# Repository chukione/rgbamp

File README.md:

# rgbamp
home etched single side rgb video amp for the n64

because my local electronic parts dealer does not sell THS7314 amp, i make this RGB amp to play on a sony PVM, with smd BC817 PNP transistors.

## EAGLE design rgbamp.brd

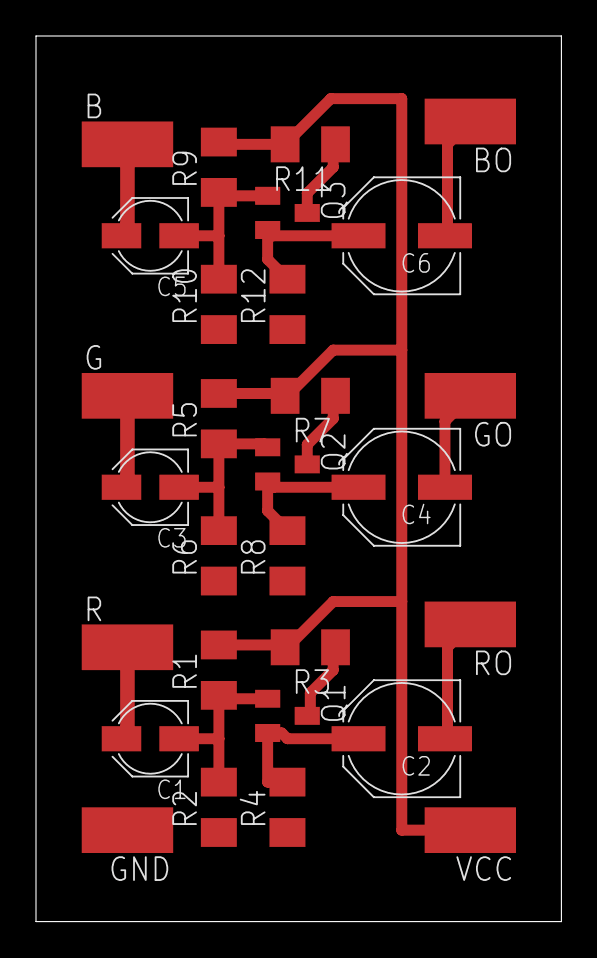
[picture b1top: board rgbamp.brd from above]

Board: 2 copper layers, 29.2 x 49.2 mm, 29 parts (0 on the bottom side), 17 nets.

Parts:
B: WIREPADSMD2,54-5,08; SMD2,54-5,08
BO: WIREPADSMD2,54-5,08; SMD2,54-5,08
C1, C3, C5: 10u; PANASONIC_B
C2, C4, C6: 220u; PANASONIC_D
G: WIREPADSMD2,54-5,08; SMD2,54-5,08
GND: WIREPADSMD2,54-5,08; SMD2,54-5,08
GO: WIREPADSMD2,54-5,08; SMD2,54-5,08
Q1, Q2, Q3: BC817-16LT1SMD; SOT23-BEC
R: WIREPADSMD2,54-5,08; SMD2,54-5,08
R1, R2, R5, R6, R9, R10: 10k; M1206
R3, R7, R11: 10; M1206
R4, R8, R12: 75; M1206
RO: WIREPADSMD2,54-5,08; SMD2,54-5,08
VCC: WIREPADSMD2,54-5,08; SMD2,54-5,08

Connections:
+5V: R1.2, R3.2, R5.2, R7.2, R9.2, R11.2, VCC.1
BIN: B.1, C5.+
BOUT: BO.1, C6.-
GIN: C3.+, G.1
GND: GND.1, R2.1, R4.1, R6.1, R8.1, R10.1, R12.1
GOUT: C4.-, GO.1
unnamed: C1.-, Q1.B, R1.1, R2.2
unnamed: C2.+, Q1.E, R4.2
unnamed: C3.-, Q2.B, R5.1, R6.2
unnamed: Q1.C, R3.1
unnamed: Q2.C, R7.1
unnamed: Q2.E, R8.2
unnamed: C5.-, Q3.B, R9.1, R10.2
unnamed: Q3.C, R11.1
unnamed: C6.+, Q3.E, R12.2
RIN: C1.+, R.1
ROUT: C2.-, RO.1

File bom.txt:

Partlist

Exported from rgbamp.brd at 10/05/18 19:37

EAGLE Version 6.1.0 Copyright (c) 1988-2012 CadSoft

Assembly variant: 

Part     Value               Package      Library        Position (mm)         Orientation

B        WIREPADSMD2,54-5,08 SMD2,54-5,08 wirepad        (5.08 43.18)          R270
BO       WIREPADSMD2,54-5,08 SMD2,54-5,08 wirepad        (24.13 44.45)         R90
C1       10u                 PANASONIC_B  resistor       (6.35 10.16)          R180
C2       220u                PANASONIC_D  resistor       (20.32 10.16)         R180
C3       10u                 PANASONIC_B  resistor       (6.35 24.13)          R180
C4       220u                PANASONIC_D  resistor       (20.32 24.13)         R180
C5       10u                 PANASONIC_B  resistor       (6.35 38.1)           R180
C6       220u                PANASONIC_D  resistor       (20.32 38.1)          R180
G        WIREPADSMD2,54-5,08 SMD2,54-5,08 wirepad        (5.08 29.21)          R270
GND      WIREPADSMD2,54-5,08 SMD2,54-5,08 wirepad        (5.08 5.08)           R90
GO       WIREPADSMD2,54-5,08 SMD2,54-5,08 wirepad        (24.13 29.21)         R90
Q1       BC817-16LT1SMD      SOT23-BEC    transistor-npn (13.97 11.43)         R270
Q2       BC817-16LT1SMD      SOT23-BEC    transistor-npn (13.97 25.4)          R270
Q3       BC817-16LT1SMD      SOT23-BEC    transistor-npn (13.97 39.37)         R270
R        WIREPADSMD2,54-5,08 SMD2,54-5,08 wirepad        (5.08 15.24)          R270
R1       10k                 M1206        resistor       (10.16 13.97)         R90
R2       10k                 M1206        resistor       (10.16 6.35)          R90
R3       10                  M1206        resistor       (15.24 15.24)         R180
R4       75                  M1206        resistor       (13.97 6.35)          R90
R5       10k                 M1206        resistor       (10.16 27.94)         R90
R6       10k                 M1206        resistor       (10.16 20.32)         R90
R7       10                  M1206        resistor       (15.24 29.21)         R180
R8       75                  M1206        resistor       (13.97 20.32)         R90
R9       10k                 M1206        resistor       (10.16 41.91)         R90
R10      10k                 M1206        resistor       (10.16 34.29)         R90
R11      10                  M1206        resistor       (15.24 43.18)         R180
R12      75                  M1206        resistor       (13.97 34.29)         R90
RO       WIREPADSMD2,54-5,08 SMD2,54-5,08 wirepad        (24.13 16.51)         R90
VCC      WIREPADSMD2,54-5,08 SMD2,54-5,08 wirepad        (24.13 5.08)          R90
